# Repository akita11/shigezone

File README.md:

# shigezone

秋葉原ラジオデパート3FのShigezoneで売っている部品の、Eagle用ライブラリ

# Author

Junichi Akita / @akita11 / akita@ifdl.jp

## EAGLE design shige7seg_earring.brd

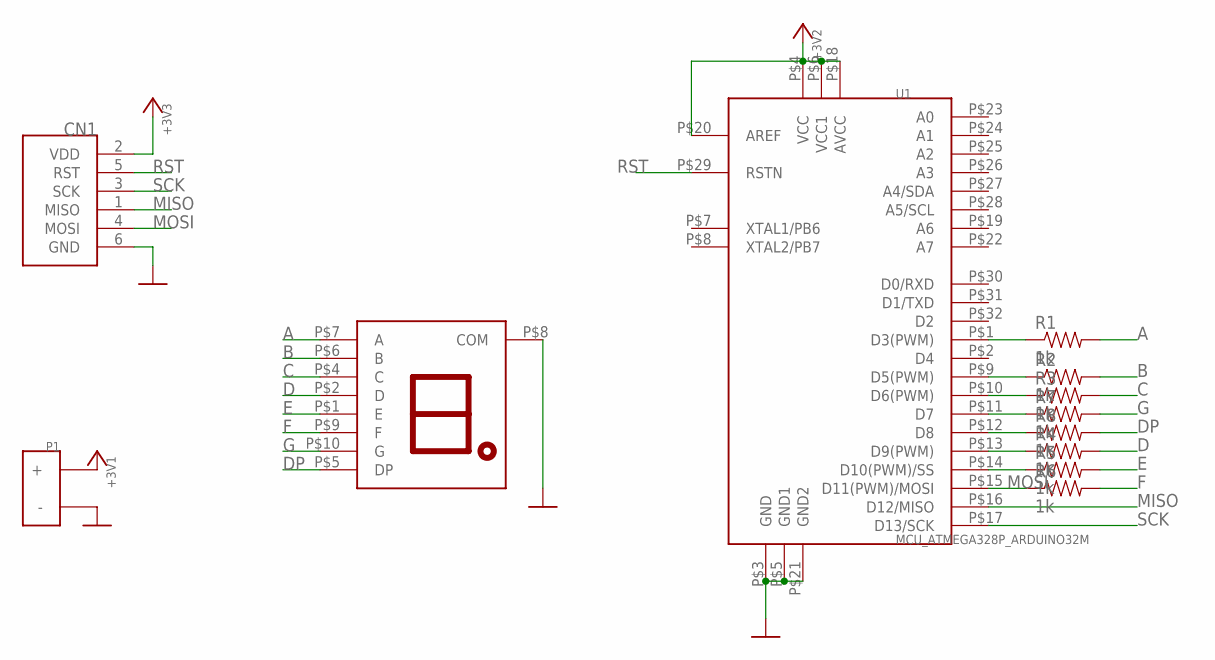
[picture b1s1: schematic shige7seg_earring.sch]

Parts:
CN1: CON_AVRISPTH; 2X03R
D1: LED_7SEG; 7SEG_10X7SMD
P1: BATTERYCOIN1220; BAT_CR1220_SMD
R1, R2, R3, R4, R5, R6, R7, R8: 1k; 0603
U1: MCU_ATMEGA328P_ARDUINO32M; QFN32

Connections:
+3V3: CN1.2 (VDD), P1.P (+), U1.P$4 (VCC), U1.P$6 (VCC1), U1.P$18 (AVCC), U1.P$20 (AREF)
A: D1.P$7 (A), R1.2
B: D1.P$6 (B), R2.2
C: D1.P$4 (C), R3.2
D: D1.P$2 (D), R4.2
DP: D1.P$5 (DP), R8.2
E: D1.P$1 (E), R5.2
F: D1.P$9 (F), R6.2
G: D1.P$10 (G), R7.2
GND: CN1.6 (GND), D1.P$8 (COM), P1.M (-), U1.P$3 (GND), U1.P$5 (GND1), U1.P$21 (GND2)
MISO: CN1.1 (MISO), U1.P$16 (D12/MISO)
MOSI: CN1.4 (MOSI), R6.1, U1.P$15 (D11(PWM)/MOSI)
unnamed: R1.1, U1.P$1 (D3(PWM))
unnamed: R2.1, U1.P$9 (D5(PWM))
unnamed: R3.1, U1.P$10 (D6(PWM))
unnamed: R7.1, U1.P$11 (D7)
unnamed: R8.1, U1.P$12 (D8)
unnamed: R4.1, U1.P$13 (D9(PWM))
unnamed: R5.1, U1.P$14 (D10(PWM)/SS)
RST: CN1.5 (RST), U1.P$29 (RSTN)
SCK: CN1.3 (SCK), U1.P$17 (D13/SCK)

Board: 2 copper layers, 12 parts (1 on the bottom side), 21 nets, no tracks yet.

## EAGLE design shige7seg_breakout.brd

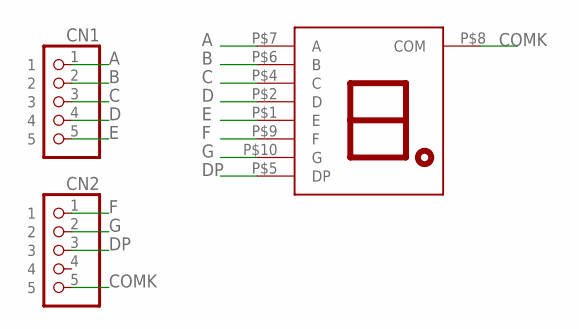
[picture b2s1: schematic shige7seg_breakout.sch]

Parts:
CN1, CN2: CON_PINHD-1X5; 1X05R
D1: LED_7SEG; 7SEG_10X7SMD

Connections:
A: CN1.1, D1.P$7 (A)
B: CN1.2, D1.P$6 (B)
C: CN1.3, D1.P$4 (C)
COMK: CN2.5, D1.P$8 (COM)
D: CN1.4, D1.P$2 (D)
DP: CN2.3, D1.P$5 (DP)
E: CN1.5, D1.P$1 (E)
F: CN2.1, D1.P$9 (F)
G: CN2.2, D1.P$10 (G)

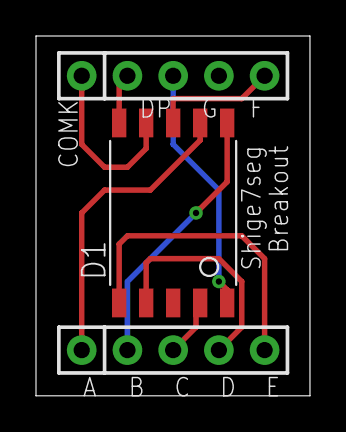
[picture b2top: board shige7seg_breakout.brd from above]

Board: 2 copper layers, 15.2 x 20.0 mm, 3 parts (0 on the bottom side), 9 nets.

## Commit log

2019-06-22 add 7segment LED in lbr
2019-06-22 shige7seg's breakout
2019-06-23 7セグメントLEDイアリング（途中）
